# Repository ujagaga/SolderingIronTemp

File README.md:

# SolderingIronTemp

I made a simple circuit to controll GORDAK soldering iron temperature. I figured I don't really need excessive precision 
since I don't really notice much difference between 350 and 380 degrees when soldering and I only use two positions anyway,
colder for small SMDs and hotter for more massive pieces. i am very happy with how this works and it is extreemly cheap.
The PCB is made for DOT PCB Perfboard (2.5mm holle dostance) so no PCB printing is necessary. Resistors and capacitors are SMD 0805 and they fit 
nicelly between two dots and under the OpAmp.

The schematic and PCB was done in KiCad, but you can just use the PNG images.

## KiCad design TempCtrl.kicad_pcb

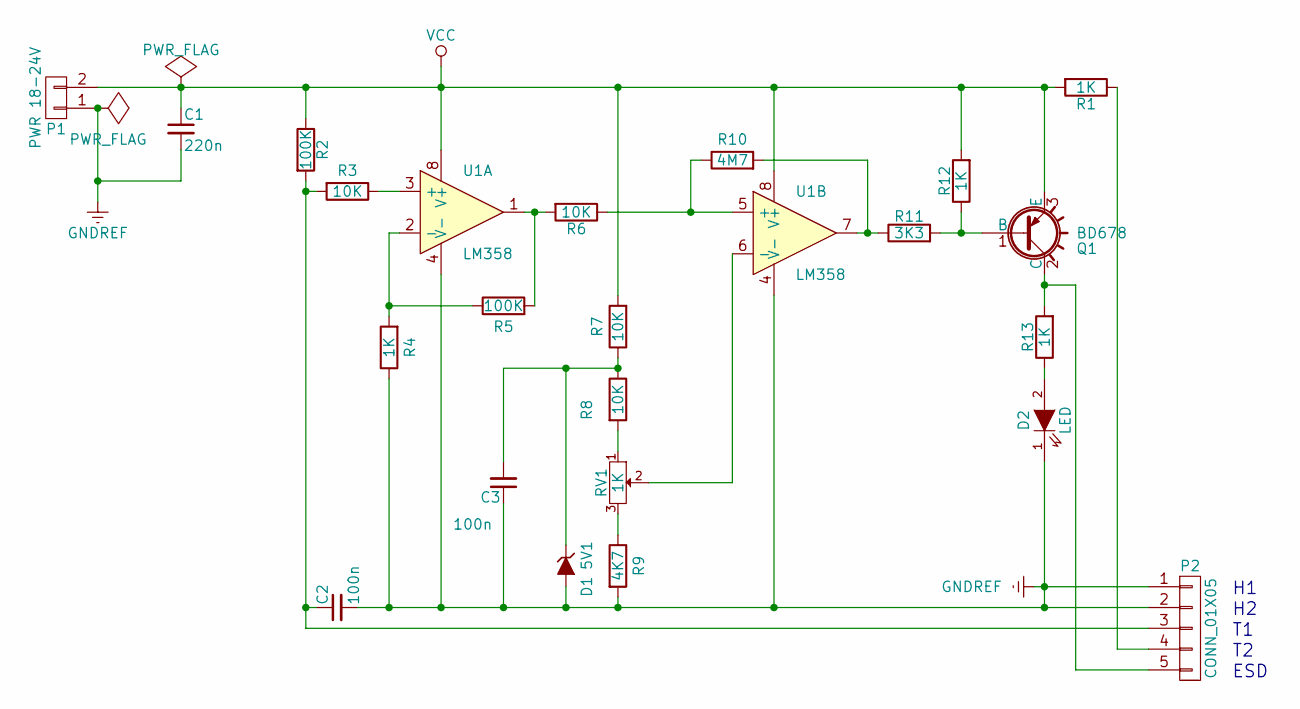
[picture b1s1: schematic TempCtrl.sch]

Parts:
C1: 220n; C_0805
C2, C3: 100n; C_0805
D1: 5V1; D_0805
D2: LED; LED_D3.0mm
P1: PWR 18-24V; Socket_Strip_Angled_1x02
P2: CONN_01X05; Socket_Strip_Straight_1x05
Q1: BD678; SOT126_SOT32_Housing_Horizontal
R1, R4, R12, R13: 1K; R_0805
R2, R5: 100K; R_0805
R3, R6, R7, R8: 10K; R_0805
R9: 4K7; R_0805
R10: 4M7; R_0805
R11: 3K3; R_0805
RV1: 1K; Potentiometer_Alps-RK16-single
U1: LM358; DIP-8_W7.62mm_Socket

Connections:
GNDREF: C1.2, C2.2, C3.1, D1.2 (A), D2.1 (K), P1.1, P2.1, P2.2, R4.1, R9.2, U1.4 (V-)
unnamed: C2.1, P2.3, R2.2, R3.2
unnamed: C3.2, D1.1 (K), R7.1, R8.1
unnamed: D2.2 (A), R13.1
unnamed: P2.4, R1.1
unnamed: P2.5, Q1.2 (C), R13.2
unnamed: Q1.1 (B), R11.2, R12.1
unnamed: R3.1, U1.3 (+)
unnamed: R4.2, R5.1, U1.2 (-)
unnamed: R5.2, R6.2, U1.1
unnamed: R8.2, RV1.1
unnamed: R9.1, RV1.3
unnamed: R6.1, R10.1, U1.5 (+)
unnamed: R10.2, R11.1, U1.7
unnamed: RV1.2, U1.6 (-)
VCC: C1.1, P1.2, Q1.3 (E), R1.2, R2.1, R7.2, R12.2, U1.8 (V+)

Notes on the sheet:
ESD

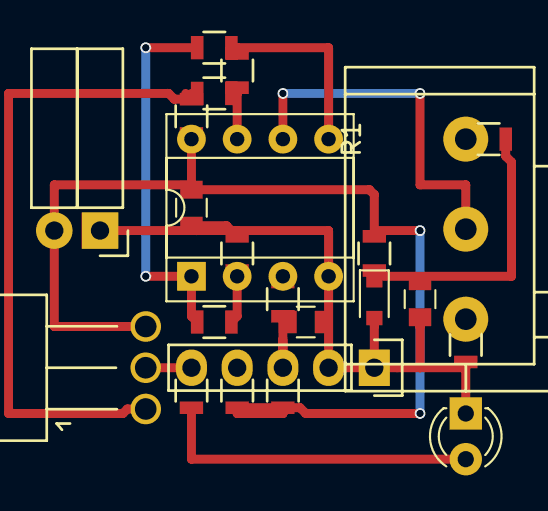
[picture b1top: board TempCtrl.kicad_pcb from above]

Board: 2 copper layers, 23 parts (0 on the bottom side), 16 nets.

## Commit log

2017-01-29 * Schematic according to experiments * optimized PCB
2017-01-31 * changed schematic to use only one Darlington * Corrected the PCB accordingly
2017-01-31 Added PNG images
2017-02-09 Final version
